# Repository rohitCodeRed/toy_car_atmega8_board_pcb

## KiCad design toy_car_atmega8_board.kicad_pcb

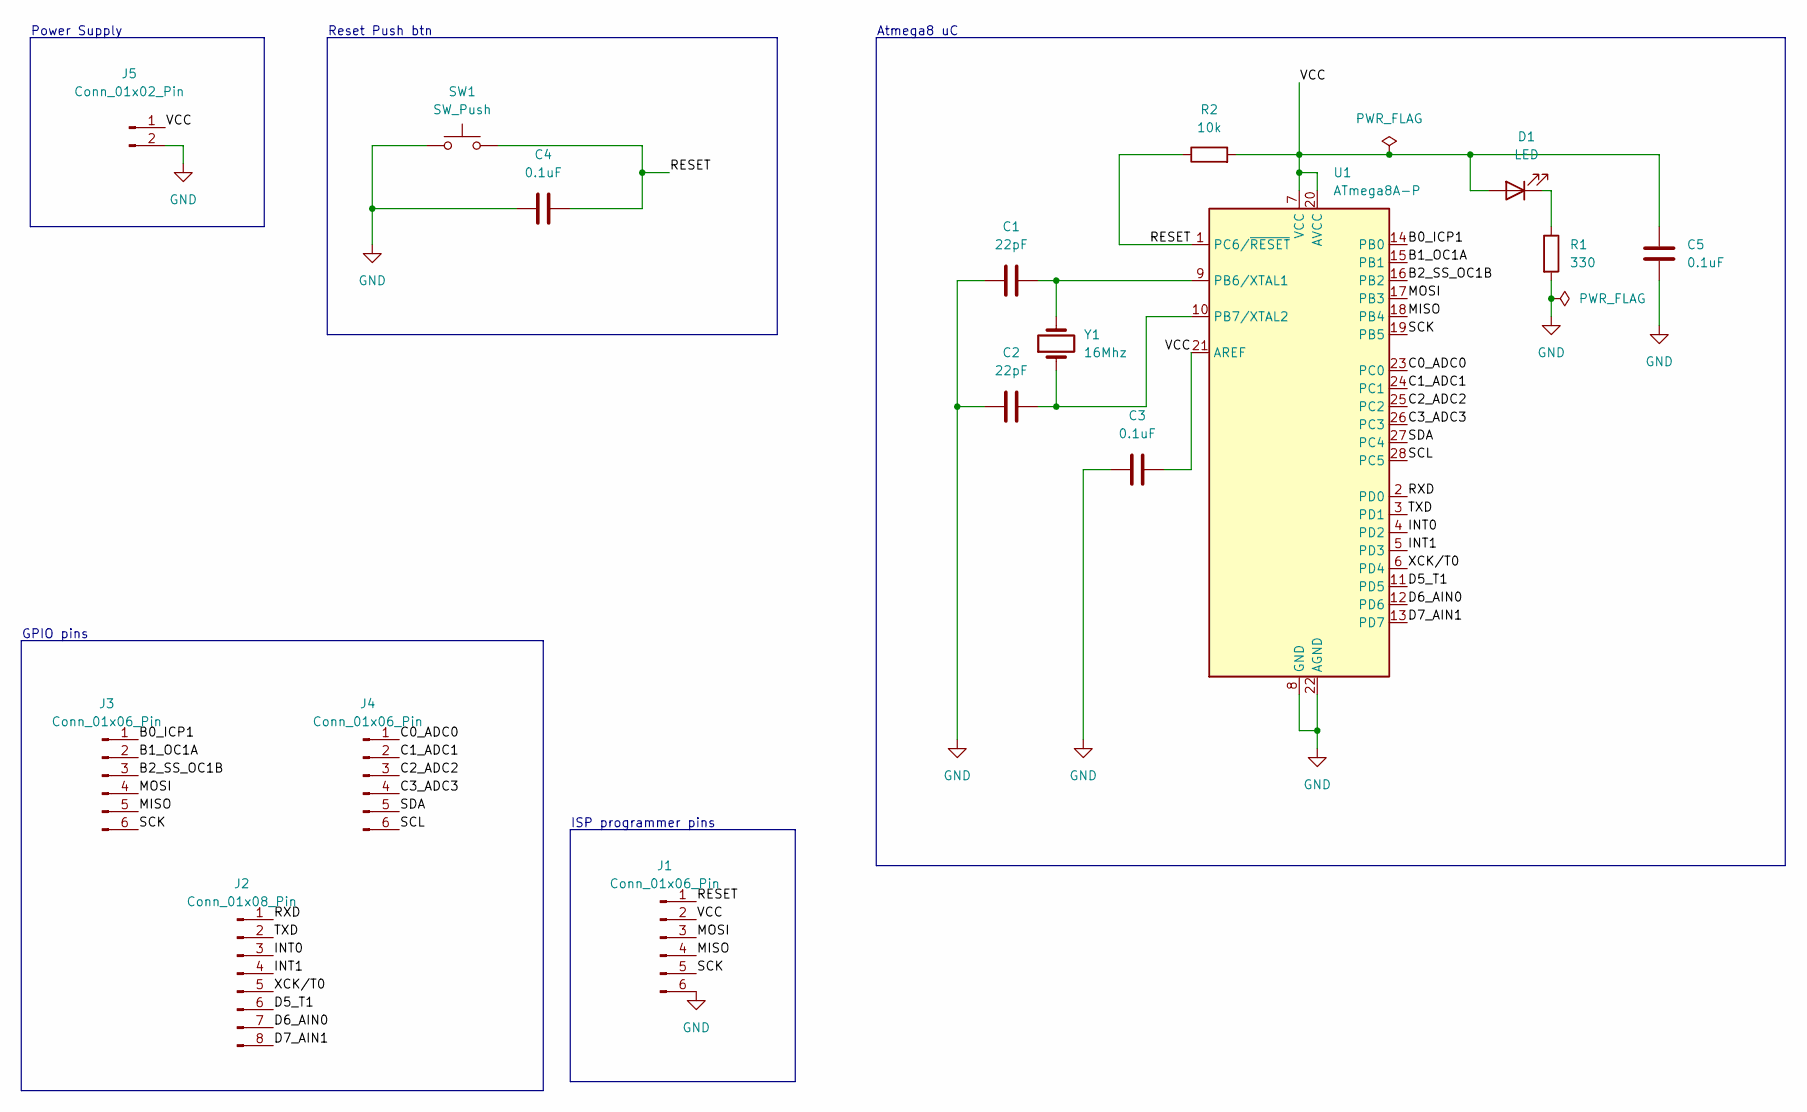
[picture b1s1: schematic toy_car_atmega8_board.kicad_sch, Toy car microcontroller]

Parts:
C1, C2: 22pF; C_Disc_D3.8mm_W2.6mm_P2.50mm
C3, C4, C5: 0.1uF; C_Disc_D3.8mm_W2.6mm_P2.50mm
D1: LED; LED_D3.0mm
J1, J3, J4: Conn_01x06_Pin; PinHeader_1x06_P2.54mm_Vertical
J2: Conn_01x08_Pin; PinHeader_1x08_P2.54mm_Vertical
J5: Conn_01x02_Pin; PinHeader_1x02_P2.54mm_Vertical
R1: 330; R_Axial_DIN0207_L6.3mm_D2.5mm_P7.62mm_Horizontal
R2: 10k; R_Axial_DIN0207_L6.3mm_D2.5mm_P7.62mm_Horizontal
SW1: SW_Push; SW_PUSH_6mm
U1: ATmega8A-P; DIP-28_W7.62mm
Y1: 16Mhz; Crystal_HC18-U_Vertical

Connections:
/B0_ICP1: J3.1, U1.14 (PB0)
/B1_OC1A: J3.2, U1.15 (PB1)
/B2_SS_OC1B: J3.3, U1.16 (PB2)
/C0_ADC0: J4.1, U1.23 (PC0)
/C1_ADC1: J4.2, U1.24 (PC1)
/C2_ADC2: J4.3, U1.25 (PC2)
/C3_ADC3: J4.4, U1.26 (PC3)
/D5_T1: J2.6, U1.11 (PD5)
/D6_AIN0: J2.7, U1.12 (PD6)
/D7_AIN1: J2.8, U1.13 (PD7)
/INT0: J2.3, U1.4 (PD2)
/INT1: J2.4, U1.5 (PD3)
/MISO: J1.4, J3.5, U1.18 (PB4)
/MOSI: J1.3, J3.4, U1.17 (PB3)
/RESET: C4.2, J1.1, R2.1, SW1.2, U1.1 (PC6/~RESET)
/RXD: J2.1, U1.2 (PD0)
/SCK: J1.5, J3.6, U1.19 (PB5)
/SCL: J4.6, U1.28 (PC5)
/SDA: J4.5, U1.27 (PC4)
/TXD: J2.2, U1.3 (PD1)
/VCC: C3.2, C5.2, D1.2 (A), J1.2, J5.1, R2.2, U1.7 (VCC), U1.20 (AVCC), U1.21 (AREF)
/XCK/T0: J2.5, U1.6 (PD4)
GND: C1.1, C2.1, C3.1, C4.1, C5.1, J1.6, J5.2, R1.2, SW1.1, U1.8 (GND), U1.22 (AGND)
unnamed: D1.1 (K), R1.1
unnamed: C1.2, U1.9 (PB6/XTAL1), Y1.2
unnamed: C2.2, U1.10 (PB7/XTAL2), Y1.1

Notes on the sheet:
GPIO pins
Atmega8 uC
ISP programmer pins
Reset Push btn
Power Supply

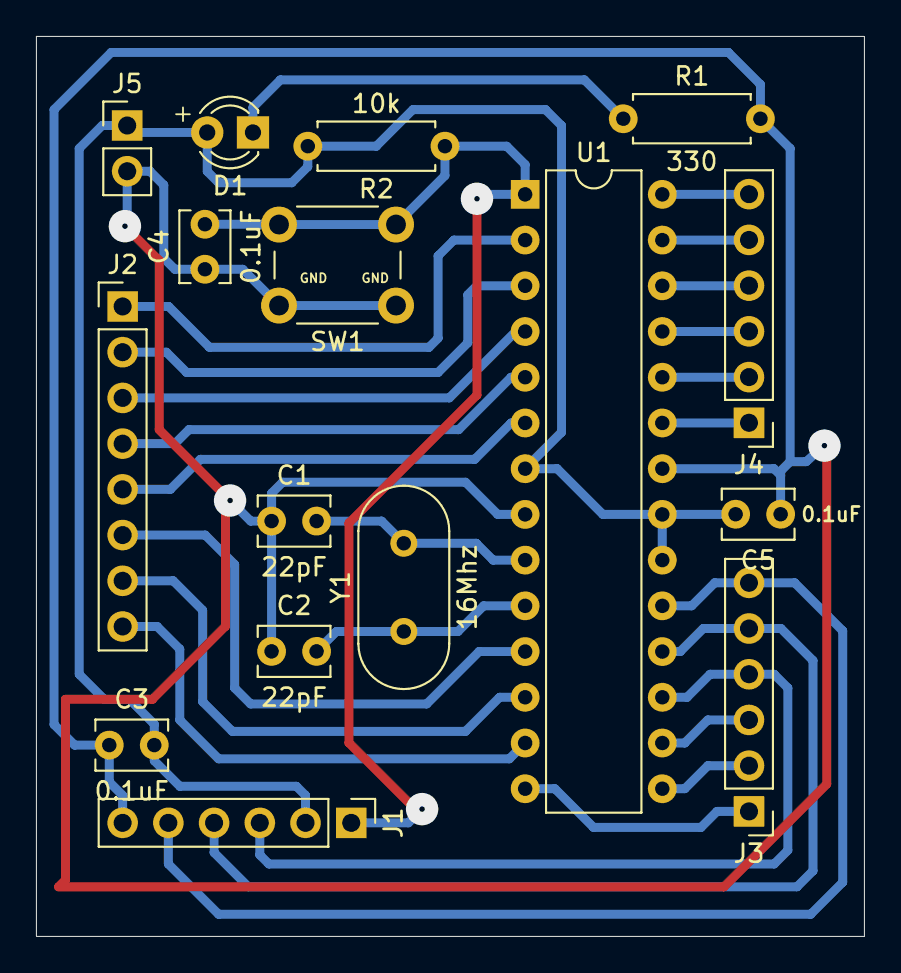
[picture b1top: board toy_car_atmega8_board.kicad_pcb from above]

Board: 2 copper layers, 46.0 x 50.0 mm, 16 parts (0 on the bottom side), 26 nets.

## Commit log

2024-08-15 Added first commit
2024-08-16 Added connector and crystal and atmega8 uC
2024-08-17 Added all labels, capacitors, resiatnce and push buttton.
2024-08-18 Added footprints and value, checked electrical connections. All good
2024-08-24 Completed pcb design and routing.
2024-09-23 Added further changes
2024-10-18 Updated pcb
